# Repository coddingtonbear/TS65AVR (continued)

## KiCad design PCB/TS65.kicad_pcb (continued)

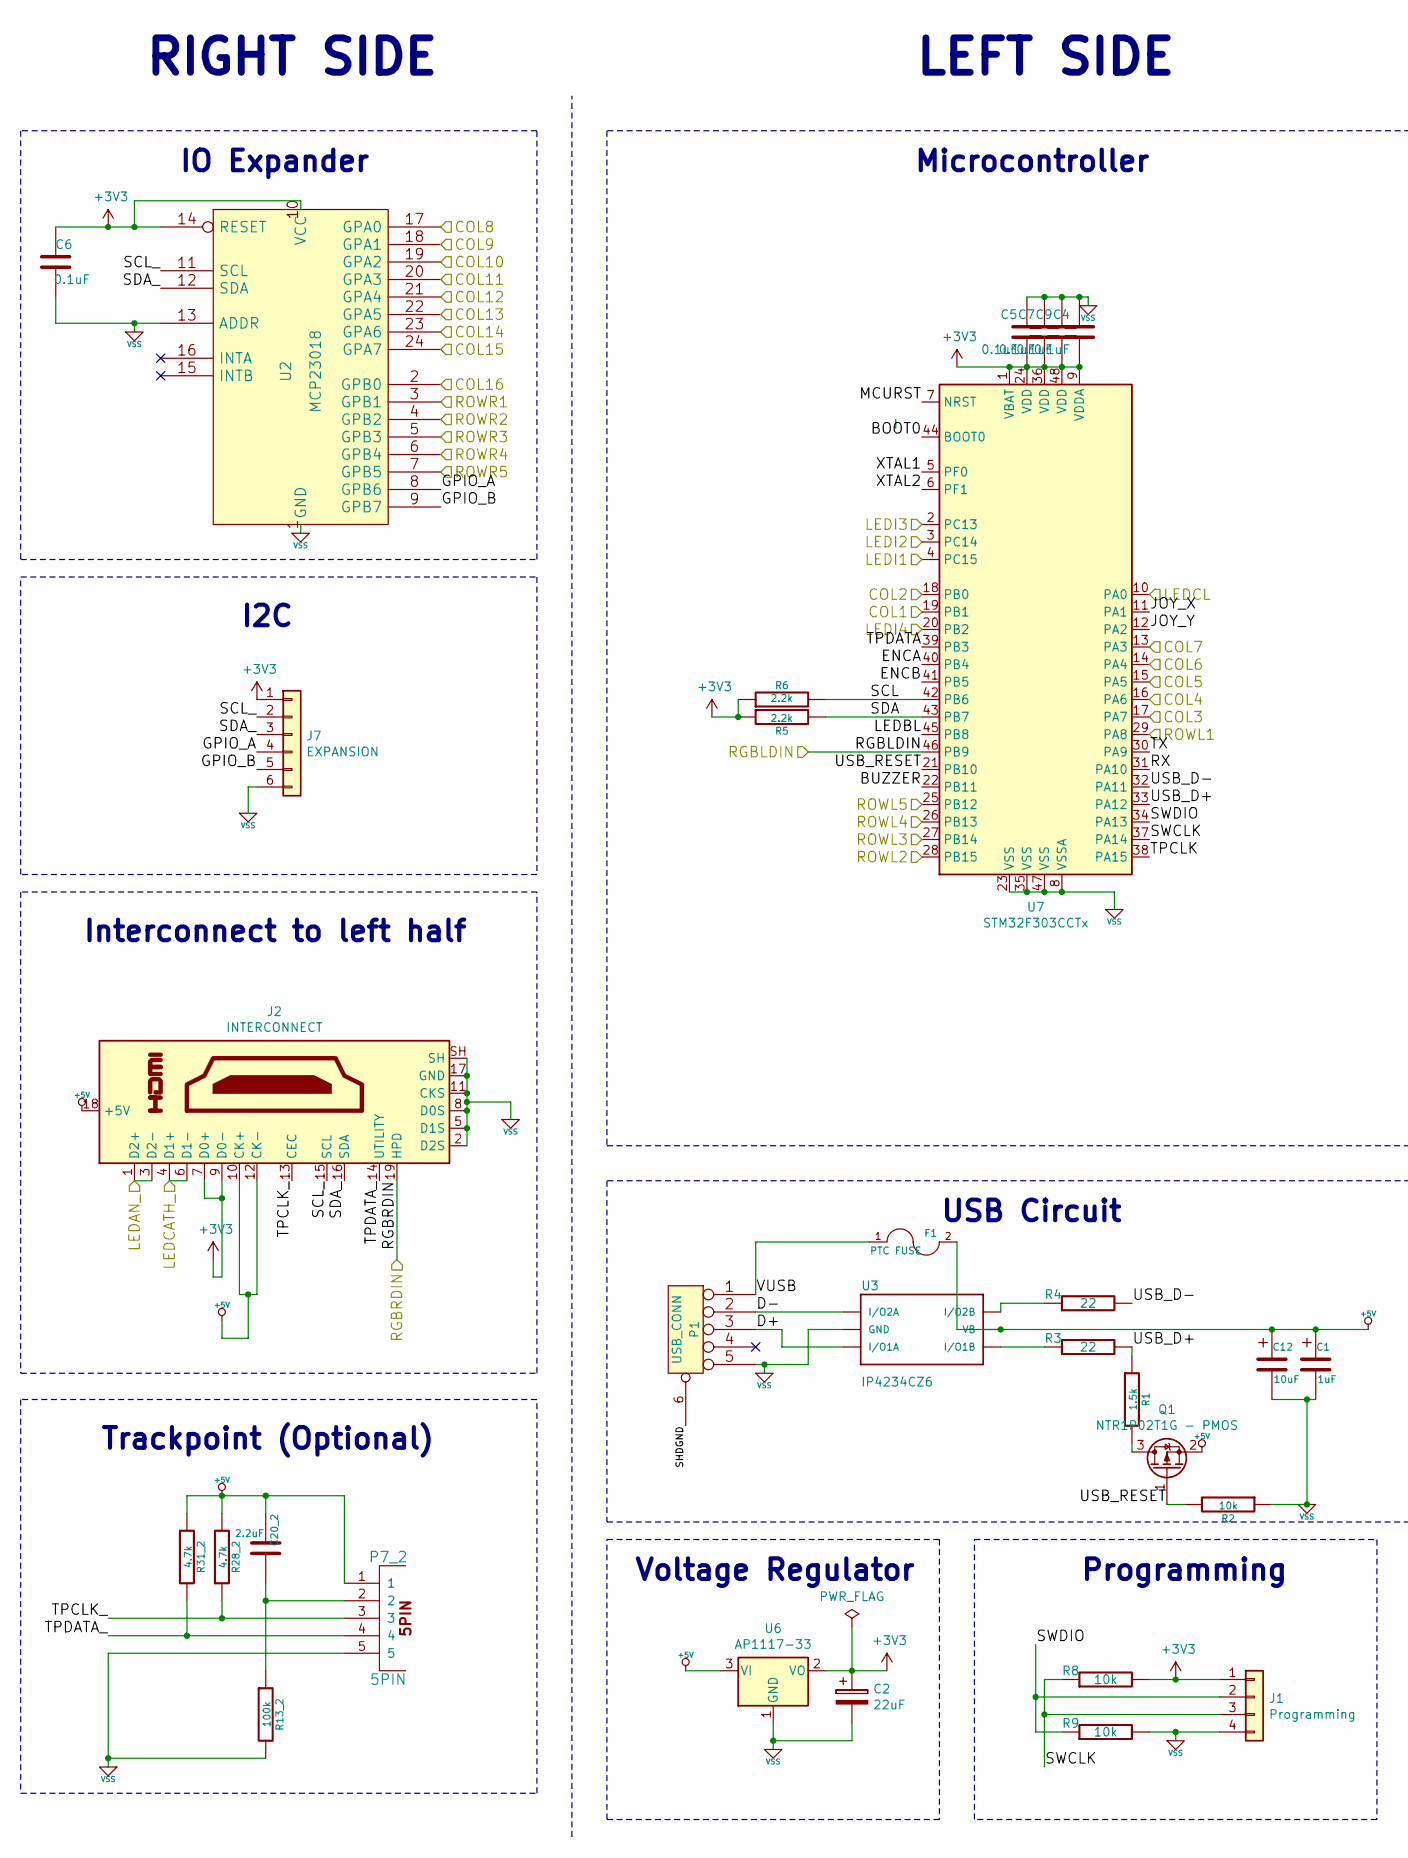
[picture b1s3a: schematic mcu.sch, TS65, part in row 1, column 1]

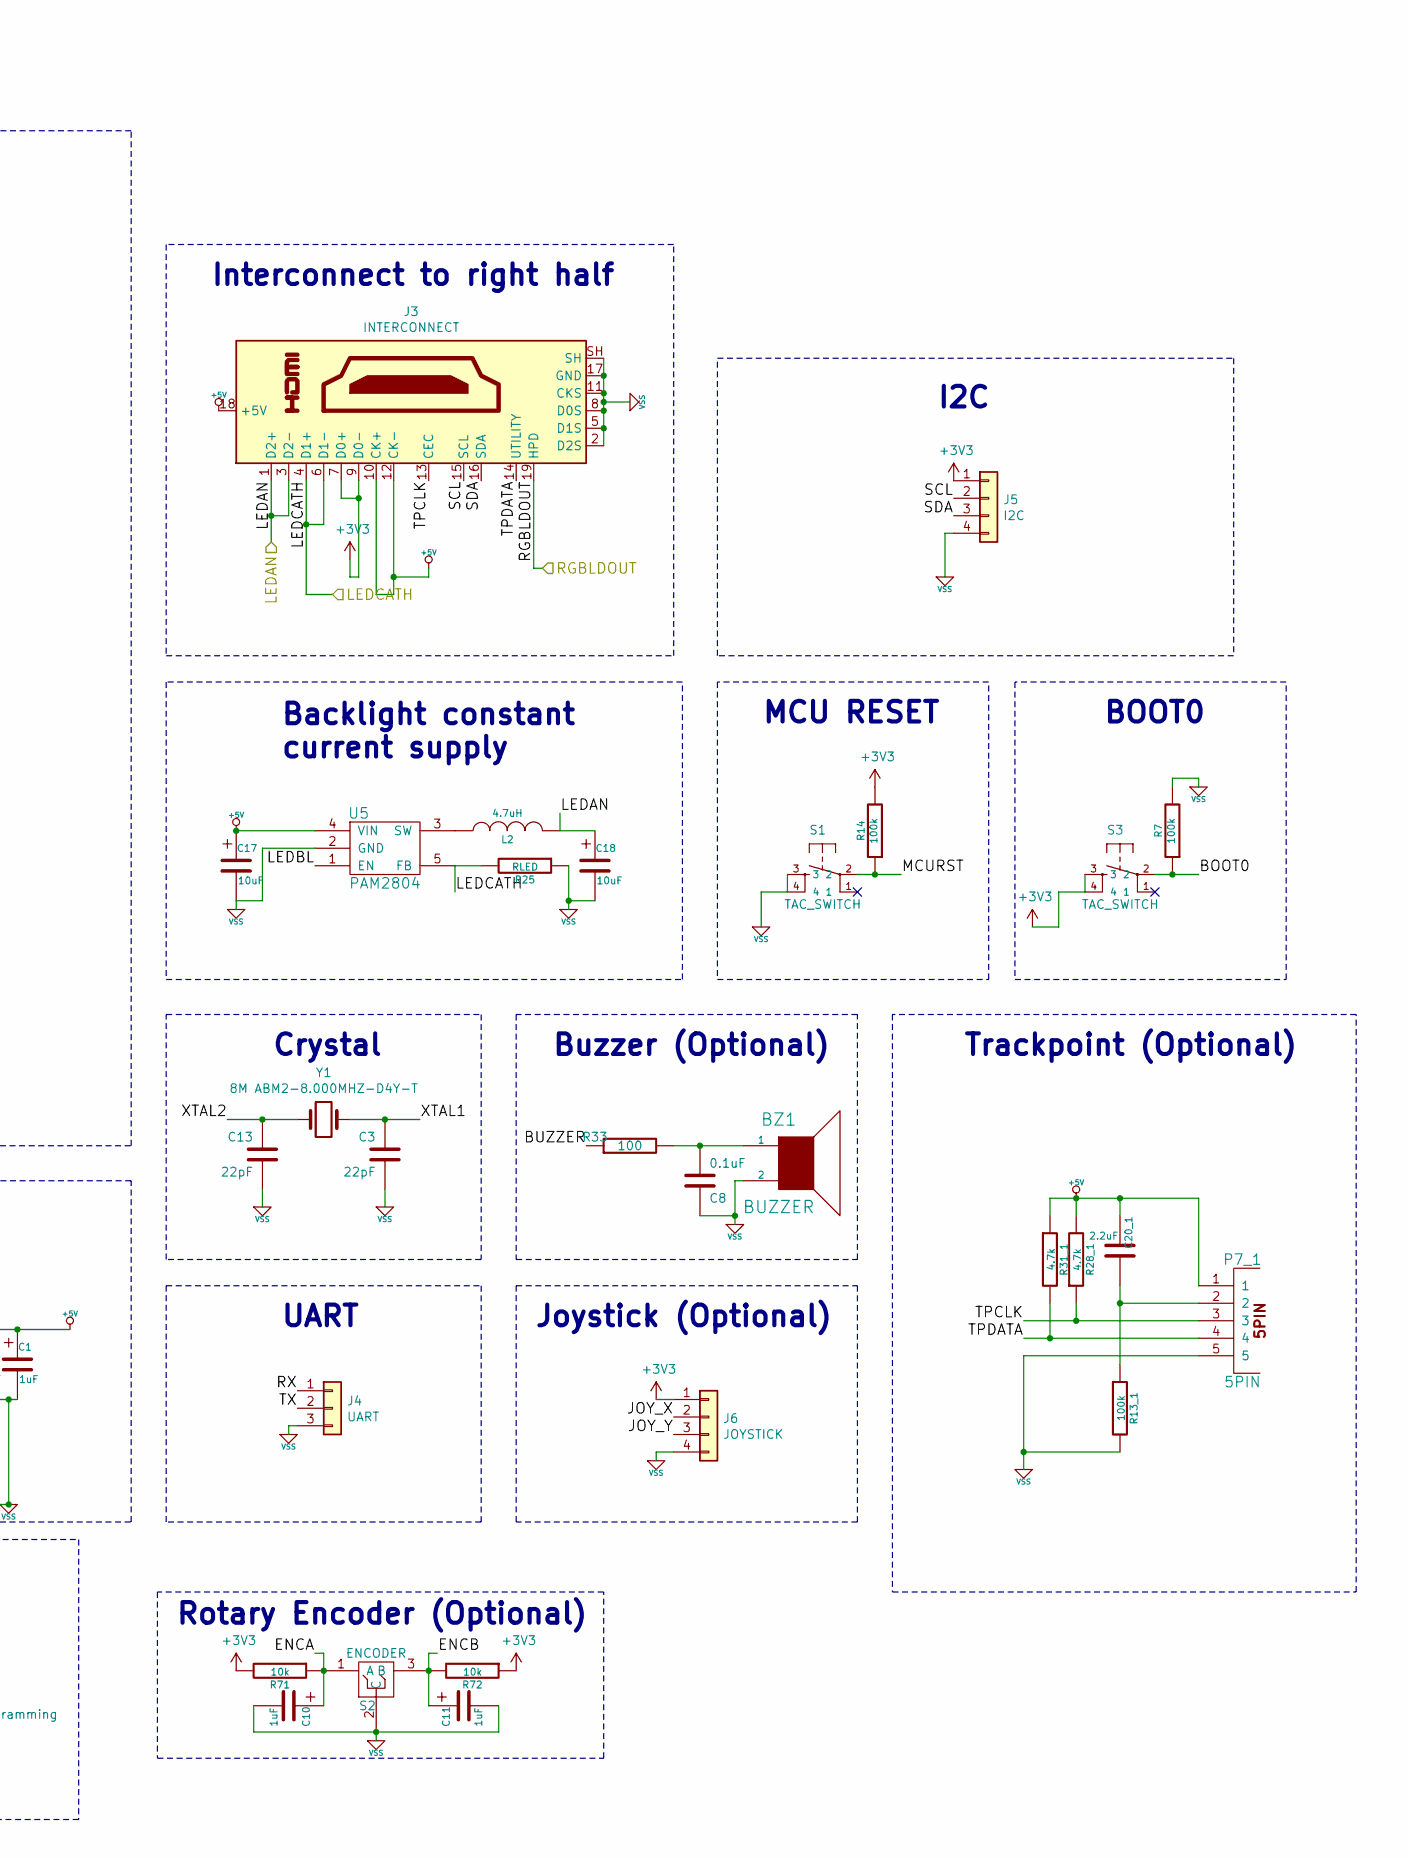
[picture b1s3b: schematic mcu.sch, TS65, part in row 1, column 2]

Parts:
BZ1: BUZZER; BUZZER_SMT
C1, C10, C11: 1uF; SMD_0805
C2: 22uF; R_1206_3216Metric
C3, C13: 22pF; SMD_0805
C4, C5, C6, C7, C8, C9: 0.1uF; SMD_0805
C12, C17, C18: 10uF; SMD_0805
C20_1, C20_2: 2.2uF; SMD_0805
F1: PTC FUSE; Fuse_SMD1206
J1: Programming; PinHeader_1x04_P2.54mm_Vertical
J2, J3: INTERCONNECT; 47151-0001
J4: UART; PinHeader_1x03_P2.54mm_Vertical
J5: I2C; PinHeader_1x04_P2.54mm_Vertical
J6: JOYSTICK; PinHeader_1x04_P2.54mm_Vertical
J7: EXPANSION; PinHeader_1x06_P2.54mm_Vertical
L2: 4.7uH; Inductor_Bourn_4mmx4mm
P1: USB_CONN; USB_Micro-B
P7_1, P7_2: 5PIN; Pin_Header_1x05
Q1: NTR1P02T1G - PMOS; SOT-23
R1: 1.5k; SMD_0805
R2, R8, R9, R71, R72: 10k; SMD_0805
R3, R4: 22; SMD_0805
R5, R6: 2.2k; SMD_0805
R7, R13_1, R13_2, R14: 100k; SMD_0805
R25: RLED; SMD_0805
R28_1, R28_2, R31_1, R31_2: 4.7k; SMD_0805
R33: 100; SMD_0805
S1, S3: TAC_SWITCH; TACT_5.2x5.2
S2: ENCODER; ENCODER_12MM
U2: MCP23018; SSOP-24
U3: IP4234CZ6; SOT457
U5: PAM2804; SOT-23-5
U6: AP1117-33; SOT-223-3_TabPin2
U7: STM32F303CCTx; LQFP-48_7x7mm_P0.5mm
Y1: 8M ABM2-8.000MHZ-D4Y-T; ABRACON-ABM2_xtal

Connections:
+3V3: C2.1, C4.2, C5.2, C6.1, C7.2, C9.2, J1.1, J2.7 (D0+), J2.9 (D0-), J3.7 (D0+), J3.9 (D0-), J5.1, J6.1, J7.1, R5.1, R6.1, R8.2, R14.2, R71.2, R72.1, S3.3, S3.4, U2.10 (VCC), U2.14 (RESET), U6.2 (VO), U7.1 (VBAT), U7.9 (VDDA), U7.24 (VDD), U7.36 (VDD), U7.48 (VDD)
+5V: C1.1, C12.1, C17.1, C20_1.2, C20_2.2, F1.2, J2.10 (CK+), J2.12 (CK-), J2.18 (+5V), J3.10 (CK+), J3.12 (CK-), J3.18 (+5V), P7_1.1, P7_2.1, Q1.2 (S), R28_1.2, R28_2.2, R31_1.1, R31_2.1, U3.5 (VB), U5.4 (VIN), U6.3 (VI); also elsewhere on the board
/Col1: U7.19 (PB1); also elsewhere on the board
/Col2: U7.18 (PB0); also elsewhere on the board
/Col3: U7.17 (PA7); also elsewhere on the board
/Col4: U7.16 (PA6); also elsewhere on the board
/Col5: U7.15 (PA5); also elsewhere on the board
/Col6: U7.14 (PA4); also elsewhere on the board
/Col7: U7.13 (PA3); also elsewhere on the board
/Col8: U2.17 (GPA0); also elsewhere on the board
/Col9: U2.18 (GPA1); also elsewhere on the board
/Col10: U2.19 (GPA2); also elsewhere on the board
/Col11: U2.20 (GPA3); also elsewhere on the board
/Col12: U2.21 (GPA4); also elsewhere on the board
/Col13: U2.22 (GPA5); also elsewhere on the board
/Col14: U2.23 (GPA6); also elsewhere on the board
/Col15: U2.24 (GPA7); also elsewhere on the board
/Col16: U2.2 (GPB0); also elsewhere on the board
/RowL1: U7.29 (PA8); also elsewhere on the board
/RowL2: U7.28 (PB15); also elsewhere on the board
/RowL3: U7.27 (PB14); also elsewhere on the board
/RowL4: U7.26 (PB13); also elsewhere on the board
/RowL5: U7.25 (PB12); also elsewhere on the board
/RowR1: U2.3 (GPB1); also elsewhere on the board
/RowR2: U2.4 (GPB2); also elsewhere on the board
/RowR3: U2.5 (GPB3); also elsewhere on the board
/RowR4: U2.6 (GPB4); also elsewhere on the board
/RowR5: U2.7 (GPB5); also elsewhere on the board
/ledmatrix/LEDAN: C18.1, J3.1 (D2+), J3.3 (D2-), L2.2; also elsewhere on the board
/ledmatrix/LEDAN_: J2.1 (D2+), J2.3 (D2-); also elsewhere on the board
/ledmatrix/LEDCATH: J3.4 (D1+), J3.6 (D1-), R25.2, U5.5 (FB); also elsewhere on the board
/ledmatrix/LEDCATH_: J2.4 (D1+), J2.6 (D1-); also elsewhere on the board
/ledmatrix/LEDCL: U7.10 (PA0); also elsewhere on the board
/ledmatrix/LEDI1: U7.4 (PC15); also elsewhere on the board
/ledmatrix/LEDI2: U7.3 (PC14); also elsewhere on the board
/ledmatrix/LEDI3: U7.2 (PC13); also elsewhere on the board
/ledmatrix/LEDI4: U7.20 (PB2); also elsewhere on the board
/ledmatrix/RGBLDIN: U7.46 (PB9); also elsewhere on the board
/ledmatrix/RGBLDOUT: J3.19 (HPD); also elsewhere on the board
/ledmatrix/RGBRDIN: J2.19 (HPD); also elsewhere on the board
/mcu/BOOT0: R7.1, S3.2, U7.44 (BOOT0)
/mcu/BUZZER: R33.1, U7.22 (PB11)
/mcu/D+: P1.3, U3.4 (I/O1A)
/mcu/D-: P1.2, U3.3 (I/O2A)
/mcu/ENCA: C10.1, R71.1, S2.1 (A), U7.40 (PB4)
/mcu/ENCB: C11.1, R72.2, S2.3 (B), U7.41 (PB5)
/mcu/GPIO_A: J7.4, U2.8 (GPB6)
/mcu/GPIO_B: J7.5, U2.9 (GPB7)
/mcu/JOY_X: J6.2, U7.11 (PA1)
/mcu/JOY_Y: J6.3, U7.12 (PA2)
/mcu/LEDBL: U5.1 (EN), U7.45 (PB8)
/mcu/MCURST: R14.1, S1.2, U7.7 (NRST)
/mcu/RX: J4.1, U7.31 (PA10)
/mcu/SCL: J3.15 (SCL), J5.2, R6.2, U7.42 (PB6)
/mcu/SCL_: J2.15 (SCL), J7.2, U2.11 (SCL)
/mcu/SDA: J3.16 (SDA), J5.3, R5.2, U7.43 (PB7)
/mcu/SDA_: J2.16 (SDA), J7.3, U2.12 (SDA)
/mcu/SHDGND: P1.6
/mcu/SWCLK: J1.3, R8.1, U7.37 (PA14)
/mcu/SWDIO: J1.2, R9.1, U7.34 (PA13)
/mcu/TPCLK: J3.13 (CEC), P7_1.3, R28_1.1, U7.38 (PA15)
/mcu/TPCLK_: J2.13 (CEC), P7_2.3, R28_2.1
/mcu/TPDATA: J3.14 (UTILITY), P7_1.4, R31_1.2, U7.39 (PB3)
/mcu/TPDATA_: J2.14 (UTILITY), P7_2.4, R31_2.2
/mcu/TX: J4.2, U7.30 (PA9)
/mcu/USB_D+: R1.1, R3.2, U7.33 (PA12)
/mcu/USB_D-: R4.2, U7.32 (PA11)
/mcu/USB_RESET: Q1.1 (G), R2.2, U7.21 (PB10)
/mcu/VUSB: F1.1, P1.1
/mcu/XTAL1: C3.1, U7.5 (PF0), Y1.2
/mcu/XTAL2: C13.1, U7.6 (PF1), Y1.1
unnamed: BZ1.1, C8.2, R33.2
unnamed: C20_1.1, P7_1.2, R13_1.1
unnamed: C20_2.1, P7_2.2, R13_2.1
unnamed: L2.1, U5.3 (SW)
unnamed: Q1.3 (D), R1.2
unnamed: R3.1, U3.6 (I/O1B)
unnamed: R4.1, U3.1 (I/O2B)
VSS: BZ1.2, C1.2, C2.2, C3.2, C4.1, C5.1, C6.2, C7.1, C8.1, C9.1, C10.2, C11.2, C12.2, C13.2, C17.2, C18.2, J1.4, J2.2 (D2S), J2.5 (D1S), J2.8 (D0S), J2.11 (CKS), J2.17 (GND), J2.SH, J3.2 (D2S), J3.5 (D1S), J3.8 (D0S), J3.11 (CKS), J3.17 (GND), J3.SH, J4.3, J5.4, J6.4, J7.6, P1.5, P7_1.5, P7_2.5, R2.1, R7.2, R9.2, R13_1.2, R13_2.2, R25.1, S1.3, S1.4, S2.2 (C), U2.1 (GND), U2.13 (ADDR), U3.2 (GND), U5.2 (GND), U6.1 (GND), U7.8 (VSSA), U7.23 (VSS), U7.35 (VSS), U7.47 (VSS); also elsewhere on the board

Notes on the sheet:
IO Expander
Trackpoint (Optional)
RIGHT SIDE
USB Circuit
Interconnect to right half
Backlight constant current supply
Crystal
MCU RESET
Buzzer (Optional)
Microcontroller
LEFT SIDE
Rotary Encoder (Optional)
BOOT0
Voltage Regulator
Programming
Interconnect to left half
I2C
UART
Joystick (Optional)

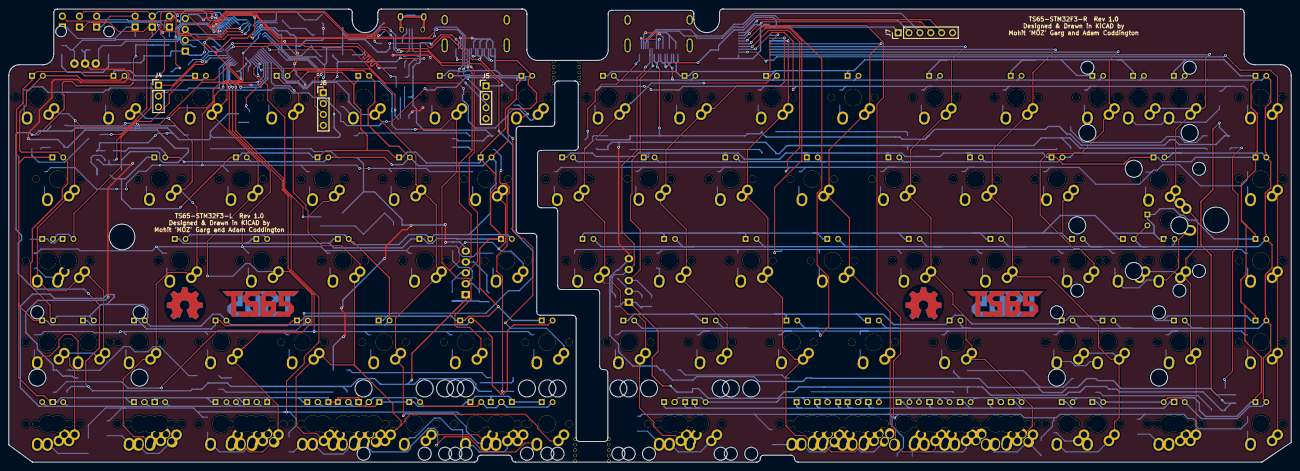
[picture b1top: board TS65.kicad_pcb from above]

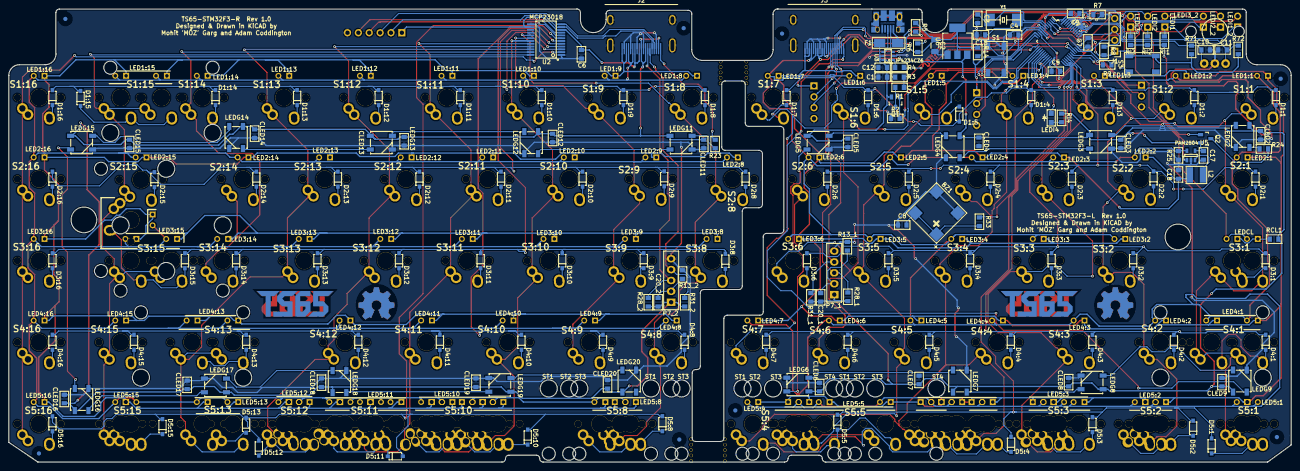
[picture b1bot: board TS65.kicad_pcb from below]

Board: 2 copper layers, 299.5 x 105.9 mm, 438 parts (192 on the bottom side), 175 nets.

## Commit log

2018-09-09 Updating schematic to use STM32F303CC microcontroller instead of ATMEGA32U4; next steps: swapping out USB3 interconnect for HDMI.
2018-09-17 Updating design to use STM32F303 instead of AVR32u4.
2018-09-25 Updating to re-include expansion port from left side.
